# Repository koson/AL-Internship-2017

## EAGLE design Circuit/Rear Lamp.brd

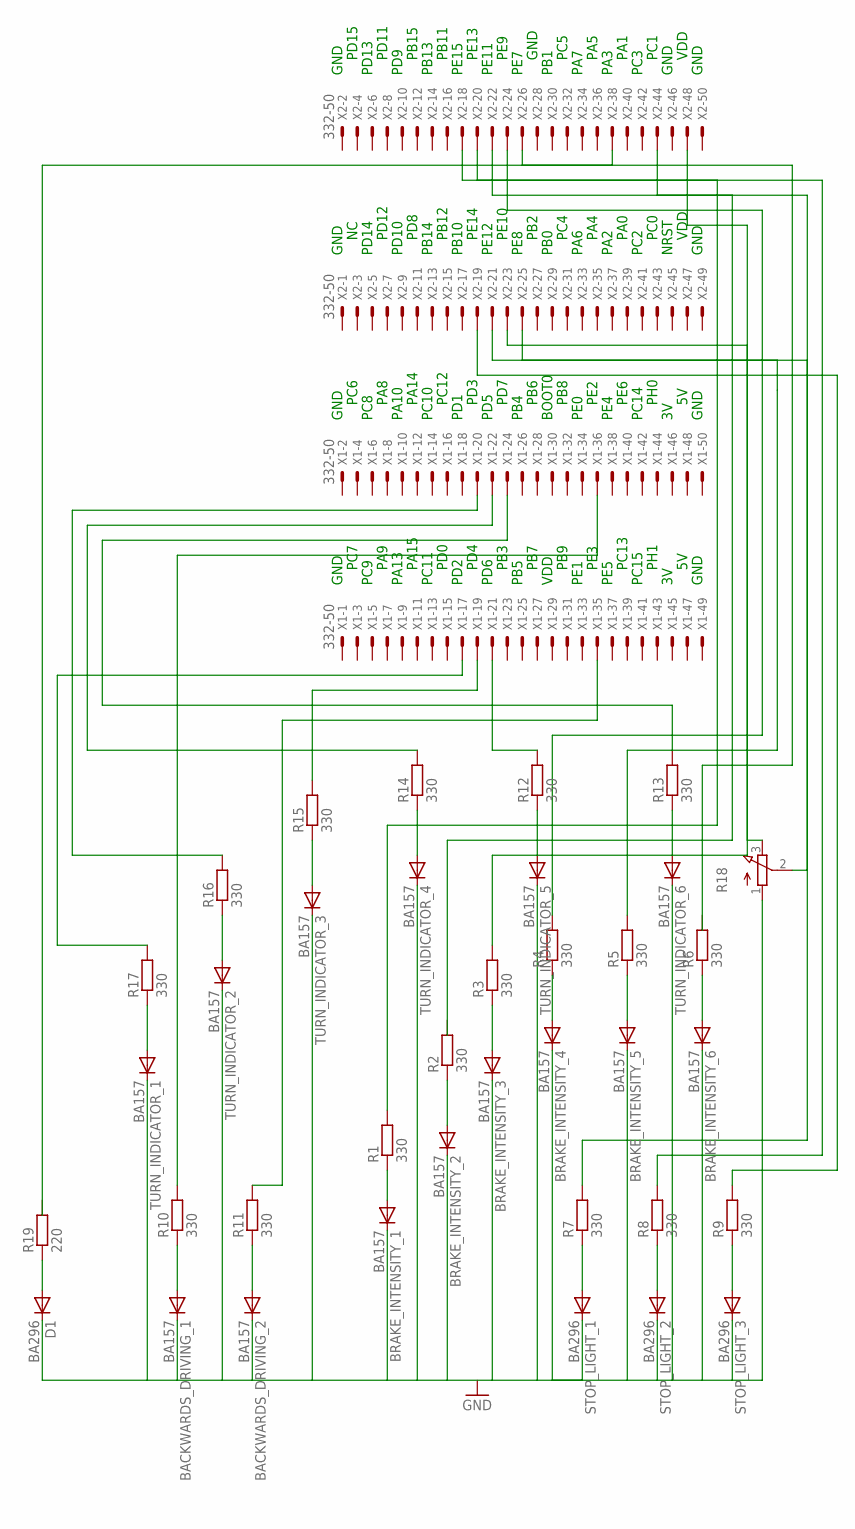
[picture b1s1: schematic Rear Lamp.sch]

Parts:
BACKWARDS_DRIVING_1, BACKWARDS_DRIVING_2: BA157; P1-10
BRAKE_INTENSITY_1, BRAKE_INTENSITY_2, BRAKE_INTENSITY_3, BRAKE_INTENSITY_4, BRAKE_INTENSITY_5, BRAKE_INTENSITY_6: BA157; P1-10
D1: BA296; P2-15
R1, R2, R3, R4, R5, R6, R7, R8, R9, R10, R11, R12, R13, R14, R15, R16, R17: 330; 0204/7
R18: 3RP/1610N
R19: 220; 0204/7
STOP_LIGHT_1, STOP_LIGHT_2, STOP_LIGHT_3: BA296; P2-15
TURN_INDICATOR_1, TURN_INDICATOR_2, TURN_INDICATOR_3, TURN_INDICATOR_4, TURN_INDICATOR_5, TURN_INDICATOR_6: BA157; P1-10
X1, X2: 332-50

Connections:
unnamed: BRAKE_INTENSITY_1.A, R1.1
unnamed: BRAKE_INTENSITY_2.A, R2.1
unnamed: BRAKE_INTENSITY_3.A, R3.1
unnamed: BRAKE_INTENSITY_4.A, R4.1
unnamed: BRAKE_INTENSITY_5.A, R5.1
unnamed: BRAKE_INTENSITY_6.A, R6.1
unnamed: R7.1, STOP_LIGHT_1.A
unnamed: R8.1, STOP_LIGHT_2.A
unnamed: R9.1, STOP_LIGHT_3.A
unnamed: BACKWARDS_DRIVING_1.A, R10.1
unnamed: BACKWARDS_DRIVING_2.A, R11.1
unnamed: R12.1, TURN_INDICATOR_5.A
unnamed: R13.1, TURN_INDICATOR_6.A
unnamed: R14.1, TURN_INDICATOR_4.A
unnamed: R15.1, TURN_INDICATOR_3.A
unnamed: R16.1, TURN_INDICATOR_2.A
unnamed: R17.1, TURN_INDICATOR_1.A
unnamed: R17.2, X1.17
unnamed: D1.A, R19.1
unnamed: R16.2, X1.20
unnamed: R15.2, X1.19
unnamed: R14.2, X1.22
unnamed: R12.2, X1.21
unnamed: R13.2, X1.24
unnamed: R10.2, X1.36
unnamed: R11.2, X1.35
unnamed: R1.2, X2.18
unnamed: R3.2, X2.23
unnamed: R4.2, X2.24
unnamed: R5.2, X2.25
unnamed: R7.2, X2.21
unnamed: R8.2, X2.20
unnamed: R9.2, X2.19
unnamed: R18.2 (S), X2.44
unnamed: R18.3 (E), X2.48
unnamed: BACKWARDS_DRIVING_1.C, BACKWARDS_DRIVING_2.C, BRAKE_INTENSITY_1.C, BRAKE_INTENSITY_2.C, BRAKE_INTENSITY_3.C, BRAKE_INTENSITY_4.C, BRAKE_INTENSITY_5.C, BRAKE_INTENSITY_6.C, D1.C, R18.1 (A), STOP_LIGHT_1.C, STOP_LIGHT_2.C, STOP_LIGHT_3.C, TURN_INDICATOR_1.C, TURN_INDICATOR_2.C, TURN_INDICATOR_3.C, TURN_INDICATOR_4.C, TURN_INDICATOR_5.C, TURN_INDICATOR_6.C

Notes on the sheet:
GND
VDD
PC1
PC3
PA1
PA3
PA5
PA7
PC5
PB1
PE7
PE9
PE11
PE13
PE15
PB11
PB13
PB15
PD9
PD11
PD13
PD15
NRST
PC0
PC2
PA0
PA2
PA4
PA6
PC4
PB0
PB2
PE8
PE10
PE12
PE14
PB10
PB12
PB14
PD8

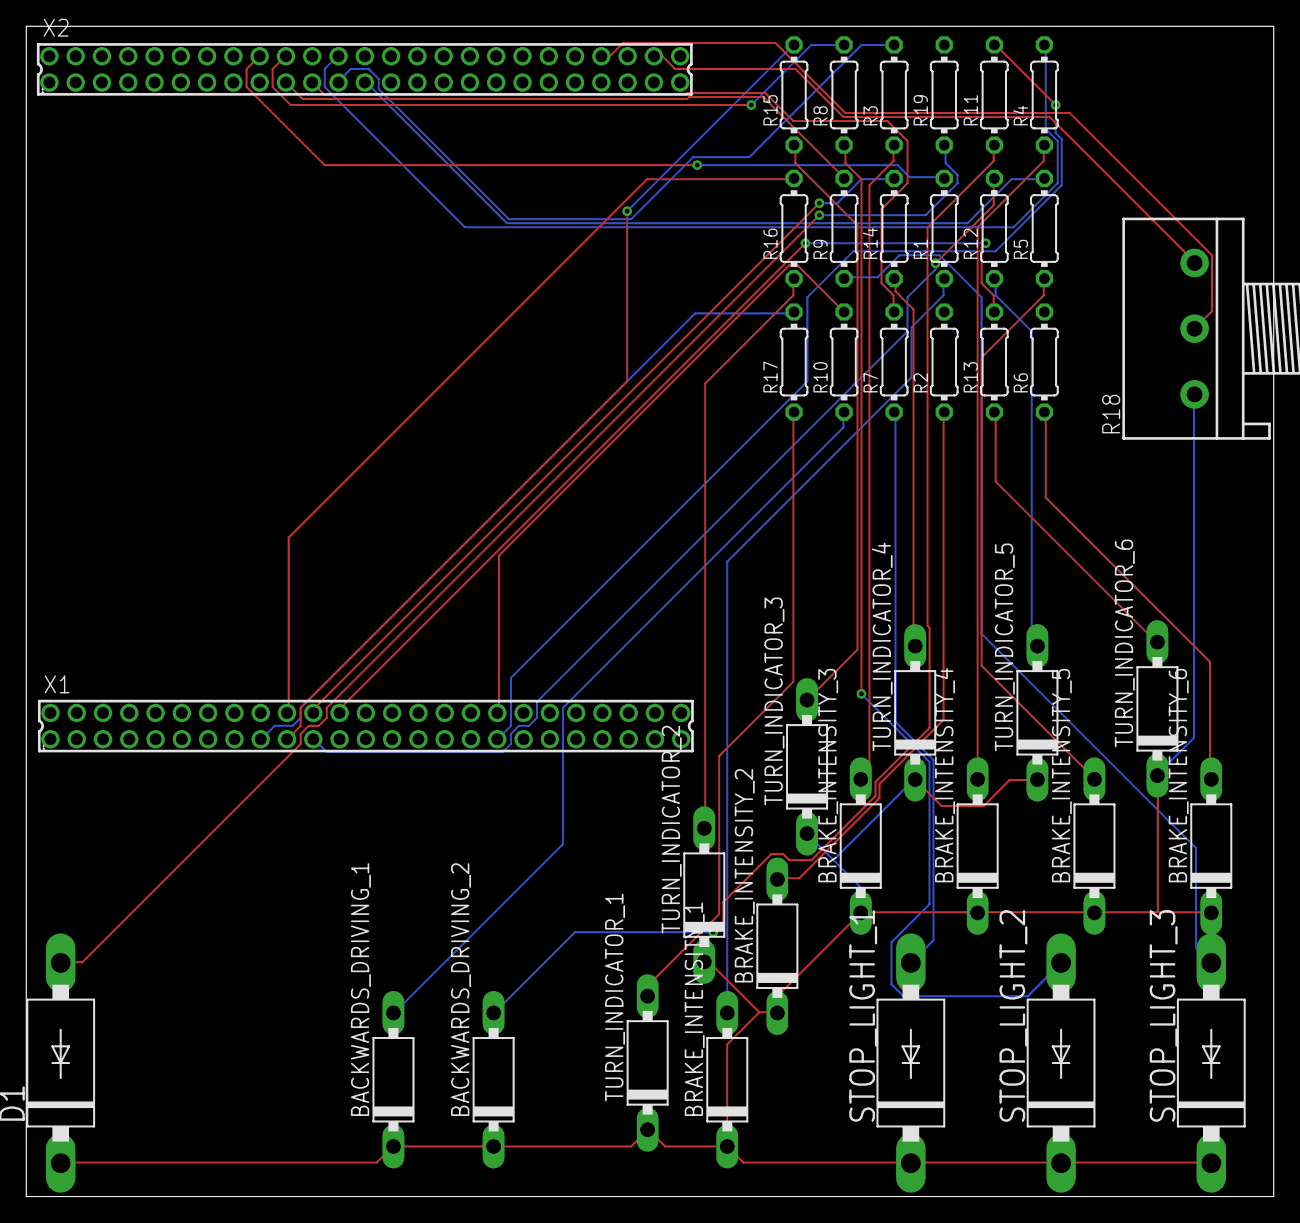
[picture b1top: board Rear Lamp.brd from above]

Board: 2 copper layers, 94.9 x 89.0 mm, 39 parts (0 on the bottom side), 36 nets.

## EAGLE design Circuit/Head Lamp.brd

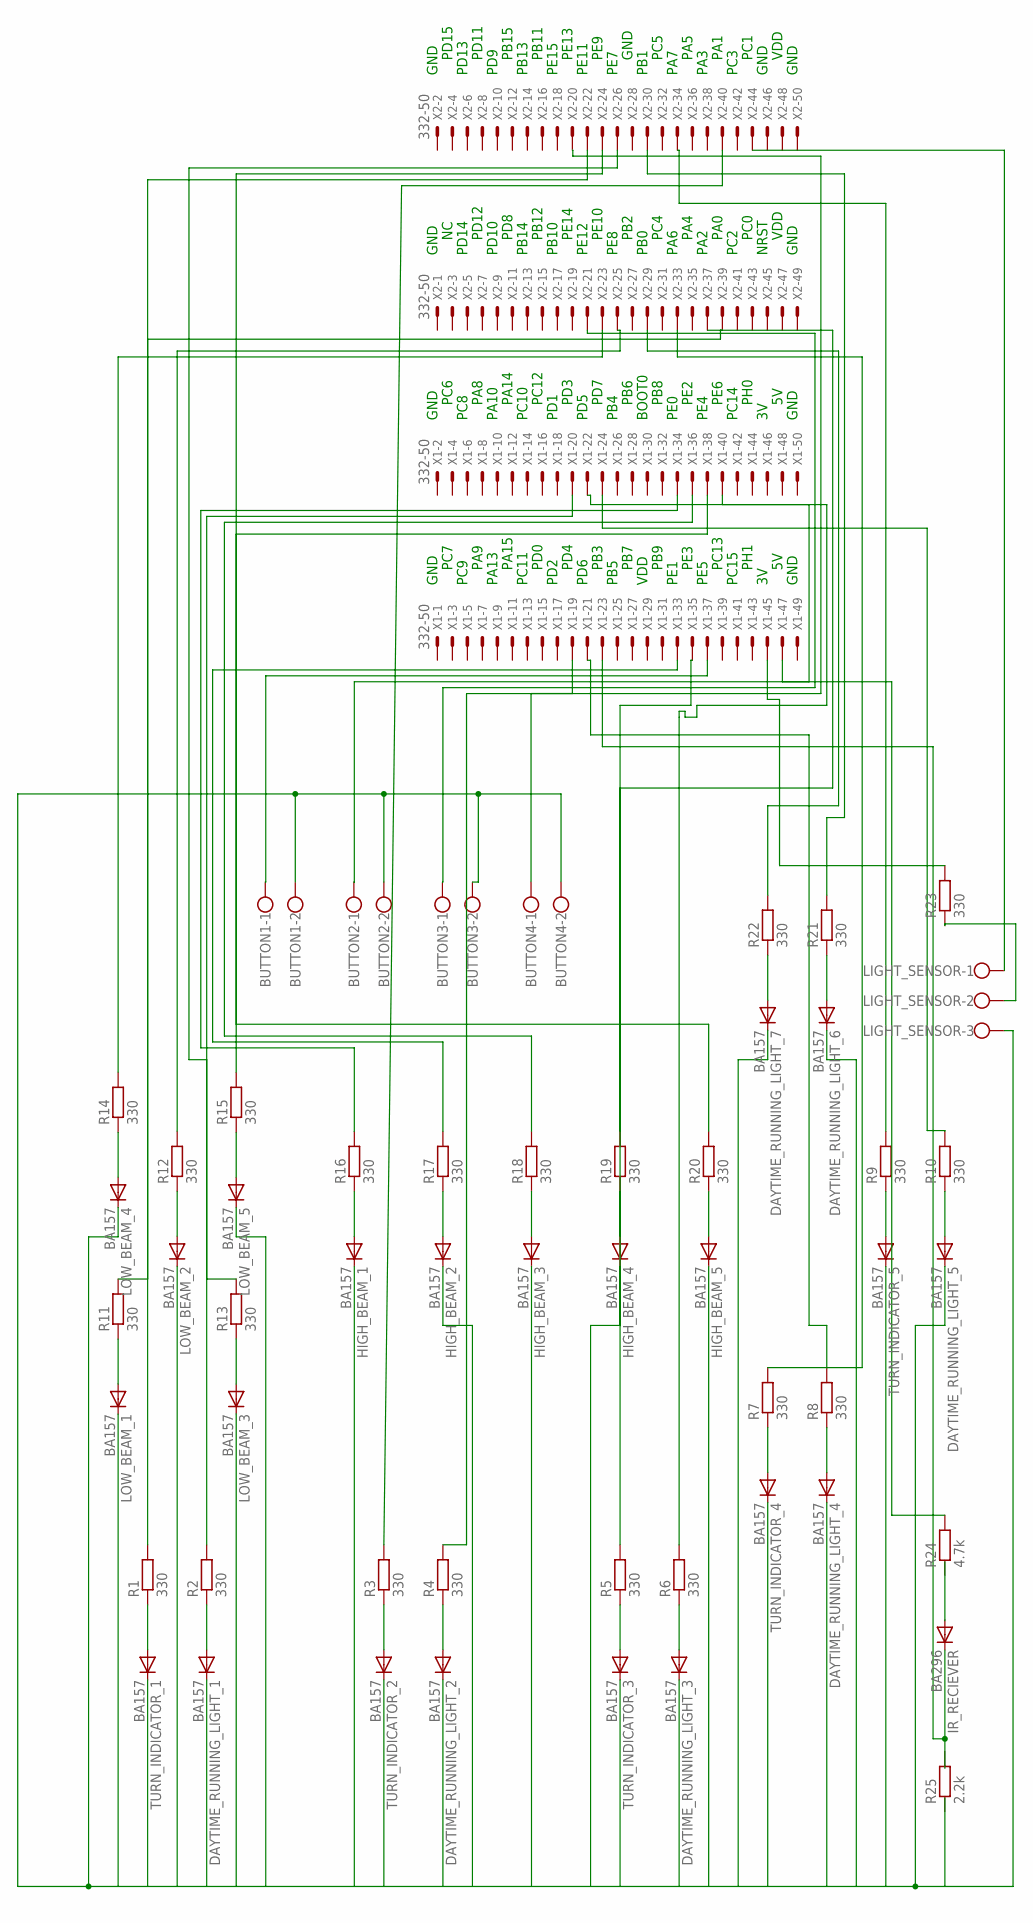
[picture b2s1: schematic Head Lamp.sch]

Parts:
BUTTON1, BUTTON2, BUTTON3, BUTTON4: W237-102
DAYTIME_RUNNING_LIGHT_1, DAYTIME_RUNNING_LIGHT_2, DAYTIME_RUNNING_LIGHT_3, DAYTIME_RUNNING_LIGHT_4, DAYTIME_RUNNING_LIGHT_5, DAYTIME_RUNNING_LIGHT_6, DAYTIME_RUNNING_LIGHT_7: BA157; P1-10
HIGH_BEAM_1, HIGH_BEAM_2, HIGH_BEAM_3, HIGH_BEAM_4, HIGH_BEAM_5: BA157; P1-10
IR_RECIEVER: BA296; P2-15
LIGHT_SENSOR: W237-103
LOW_BEAM_1, LOW_BEAM_2, LOW_BEAM_3, LOW_BEAM_4, LOW_BEAM_5: BA157; P1-10
R1, R2, R3, R4, R5, R6, R7, R8, R9, R10, R11, R12, R13, R14, R15, R16, R17, R18, R19, R20, R21, R22, R23: 330; 0204/7
R24: 4.7k; 0204/7
R25: 2.2k; 0204/7
TURN_INDICATOR_1, TURN_INDICATOR_2, TURN_INDICATOR_3, TURN_INDICATOR_4, TURN_INDICATOR_5: BA157; P1-10
X1, X2: 332-50

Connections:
unnamed: DAYTIME_RUNNING_LIGHT_1.A, R2.1
unnamed: R3.1, TURN_INDICATOR_2.A
unnamed: DAYTIME_RUNNING_LIGHT_2.A, R4.1
unnamed: R1.1, TURN_INDICATOR_1.A
unnamed: R5.1, TURN_INDICATOR_3.A
unnamed: DAYTIME_RUNNING_LIGHT_3.A, R6.1
unnamed: R7.1, TURN_INDICATOR_4.A
unnamed: DAYTIME_RUNNING_LIGHT_4.A, R8.1
unnamed: R9.1, TURN_INDICATOR_5.A
unnamed: DAYTIME_RUNNING_LIGHT_5.A, R10.1
unnamed: LOW_BEAM_1.A, R11.1
unnamed: LOW_BEAM_2.A, R12.1
unnamed: LOW_BEAM_3.A, R13.1
unnamed: LOW_BEAM_4.A, R14.1
unnamed: LOW_BEAM_5.A, R15.1
unnamed: HIGH_BEAM_1.A, R16.1
unnamed: HIGH_BEAM_2.A, R17.1
unnamed: HIGH_BEAM_3.A, R18.1
unnamed: HIGH_BEAM_4.A, R19.1
unnamed: HIGH_BEAM_5.A, R20.1
unnamed: DAYTIME_RUNNING_LIGHT_6.A, R21.1
unnamed: DAYTIME_RUNNING_LIGHT_7.A, R22.1
unnamed: BUTTON1.1, X1.37
unnamed: BUTTON2.1, X1.40
unnamed: BUTTON3.1, X2.21
unnamed: BUTTON4.1, X2.20
unnamed: R16.2, X1.34
unnamed: R17.2, X1.33
unnamed: R18.2, X1.36
unnamed: R19.2, X1.35
unnamed: R20.2, X1.38
unnamed: R13.2, X2.26
unnamed: R12.2, X2.25
unnamed: R15.2, X2.24
unnamed: R14.2, X2.23
unnamed: R11.2, X2.22
unnamed: R2.2, X1.20
unnamed: R4.2, X1.19
unnamed: R6.2, X1.22
unnamed: R22.2, X2.29
unnamed: R8.2, X1.21
unnamed: R10.2, X1.24
unnamed: R1.2, X2.39
unnamed: R3.2, X2.40
unnamed: R5.2, X2.37
unnamed: R21.2, X2.30
unnamed: R7.2, X2.33
unnamed: R9.2, X2.34
unnamed: BUTTON1.2, BUTTON2.2, BUTTON3.2, BUTTON4.2, DAYTIME_RUNNING_LIGHT_1.C, DAYTIME_RUNNING_LIGHT_2.C, DAYTIME_RUNNING_LIGHT_3.C, DAYTIME_RUNNING_LIGHT_4.C, DAYTIME_RUNNING_LIGHT_5.C, DAYTIME_RUNNING_LIGHT_6.C, DAYTIME_RUNNING_LIGHT_7.C, HIGH_BEAM_1.C, HIGH_BEAM_2.C, HIGH_BEAM_3.C, HIGH_BEAM_4.C, HIGH_BEAM_5.C, LIGHT_SENSOR.3, LOW_BEAM_1.C, LOW_BEAM_2.C, LOW_BEAM_3.C, LOW_BEAM_4.C, LOW_BEAM_5.C, TURN_INDICATOR_1.C, TURN_INDICATOR_2.C, TURN_INDICATOR_3.C, TURN_INDICATOR_4.C, TURN_INDICATOR_5.C
unnamed: R24.2, X1.47
unnamed: LIGHT_SENSOR.1, X2.44
unnamed: LIGHT_SENSOR.2, R23.1
unnamed: R23.2, X1.45

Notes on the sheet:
GND
VDD
PC1
PC3
PA1
PA3
PA5
PA7
PC5
PB1
PE7
PE9
PE11
PE13
PE15
PB11
PB13
PB15
PD9
PD11
PD13
PD15
NRST
PC0
PC2
PA0
PA2
PA4
PA6
PC4
PB0
PB2
PE8
PE10
PE12
PE14
PB10
PB12
PB14
PD8

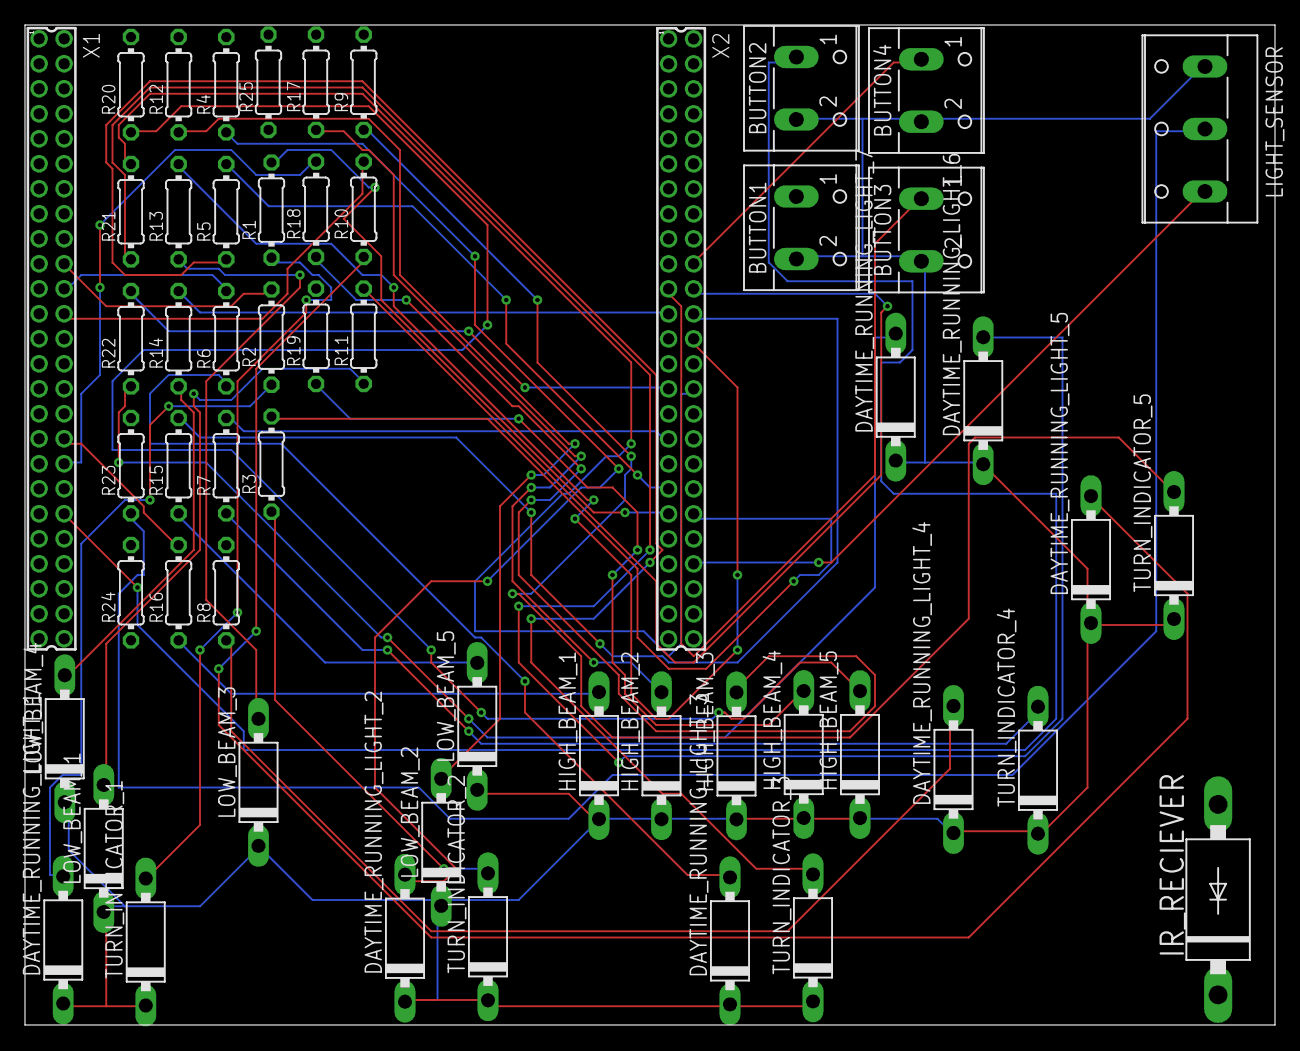
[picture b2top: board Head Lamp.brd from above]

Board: 2 copper layers, 100.0 x 80.0 mm, 55 parts (0 on the bottom side), 53 nets.

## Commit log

2017-07-12 CAN first try (not working)
2017-07-12 PWM_led_dimming_demo
    A simple demo using pwm. Timers TIM2(CH1->PA0, CH2->PA1 ,CH3->PA2) and TIM3(CH1->PA6, CH2->PA7) are used.
2017-07-13 "Initail variant for IR"
2017-07-13 Removed the old CAN
2017-07-13 CAN 0.1
    CAN transmit and recieve loop
    Transmitted message is not correct
2017-07-14 .project
2017-07-14 Added CubeMX config
2017-07-14 CAN Tx Working
2017-07-14 CAN Rx Working
    Added can filter that passes everything
2017-07-17 working but not synchronized
2017-07-17 Working ADC (brake levels)
2017-07-17 All leds connected
    Demo using front and back leds
2017-07-17 Removed old can
2017-07-17 Addet adc (Brake levels)
2017-07-17 Added Ursu's project
2017-07-17 Leds low beam added
2017-07-17 Cleared adc only
2017-07-17 ADC+LED+CAN
2017-07-18 Working :>
2017-07-18 implemented messages
2017-07-18 Organised
2017-07-18 Added IR (going to merge)
2017-07-18 deleted stuff
2017-07-18 Removed trash
2017-07-18 "implemented CANdecode for IR"
2017-07-19 Added IR reciever
2017-07-19 Added dimming on Turn Indicator
2017-07-19 IR receiver code refactory
2017-07-20 Updated IR part for synchronization
2017-07-20 Updated Port Init
2017-07-20 solved the "failed" case
2017-07-20 added Rear Lamp project
2017-07-20 Working Rear Lamp
2017-07-20 Added push button(short/long press) for high beam
2017-07-20 Minor changes
2017-07-20 Reciever and tranciever working with can
2017-07-21 eliminated the failed messsage
2017-07-21 Separated leds and buttons functions
    Added 4 files, with specific functions, Timer that manages the buttons to turn on/off leds
2017-07-21 Synchronized IR transmission
2017-07-21 Added MAN/AUTO mode
2017-07-21 Added comments to leds functions
2017-07-21 Removed rear lamp code
2017-07-21 Improved main code
2017-07-21 Changed Pins for buttons
2017-07-21 Removed front led port/pin from rear lights
2017-07-24 Deleted old files
2017-07-25 added distance sensor
2017-07-26 using TIM5 for distance sensor too
2017-07-26 Light sensor working
2017-07-27 Refactory on front lamp
2017-07-27 Light senosr good
2017-07-28 Refactory on the code part.2
2017-07-28 Refactory on the rear lamp
2017-07-28 Resolved DRL turning on while turn indicator is on
2017-07-28 Updated DRL functions
2017-07-28 Added low beam function for night mode
2017-07-28 Added brake signal when brake
2017-07-28 Separated light sensor functions
2017-07-28 Added toggle mode for buttons
2017-07-31 Added Light sensor Functions
2017-07-31 Added more leds to rear lamp
2017-07-31 Added osbtacle detection
2017-07-31 Added turn indicator on REAR LAMP
2017-07-31 Added Leds function special files
2017-08-01 Changed brake levels
2017-08-01 Updated Leds Functions
2017-08-01 updated main
2017-08-01 Added signals
2017-08-01 IR working properly
2017-08-01 Finally work
2017-08-01 Warning
2017-08-02 Added comments to LEDs functions on rear Lights
2017-08-02 Renamed Rear Lamp Project
2017-08-02 Restructured
2017-08-02 added stdint.h
2017-08-02 deletted unused variables
2017-08-02 Restructure
2017-08-02 Renamed Front Project
2017-08-02 Deleted old folder
2017-08-02 Improved Light sensor functions
2017-08-02 Improved High beam sensor functionality
2017-08-03 Low Beam flag Added
2017-08-03 New source file added
    Init functions were moved from main
2017-08-03 Changed can variables
2017-08-03 Added CANoe interface
2017-08-03 Added IR LED on interface
2017-08-03 Canoe Update
2017-08-03 Emergency Brake and Demo added
2017-08-04 Moved transmit function in IR module from main
2017-08-04 warnings solved
2017-08-04 Improved IR communication speed
2017-08-04 Added source file for init on Rear Lamp
2017-08-04 Emergency brake review
2017-08-04 Added source files for ADC and CAN
2017-08-04 Update CAN functions
2017-08-04 Front Lamp light sensor improved
2017-08-04 More comments added to Front Lamp, Turn indicator modified
2017-08-04 Auto stash before merge of "Test_Buttons_Branch" and "origin/Test_Buttons_Branch"
2017-08-04 Addeds comments on IR functions
2017-08-04 added more coments on IR functions
2017-08-04 Added Demo on TI long press
2017-08-04 added coments on IR timers
2017-08-04 demo update
2017-08-07 Renamed Head Lamp
2017-08-07 Update on light sensor
2017-08-08 Added circuit board
